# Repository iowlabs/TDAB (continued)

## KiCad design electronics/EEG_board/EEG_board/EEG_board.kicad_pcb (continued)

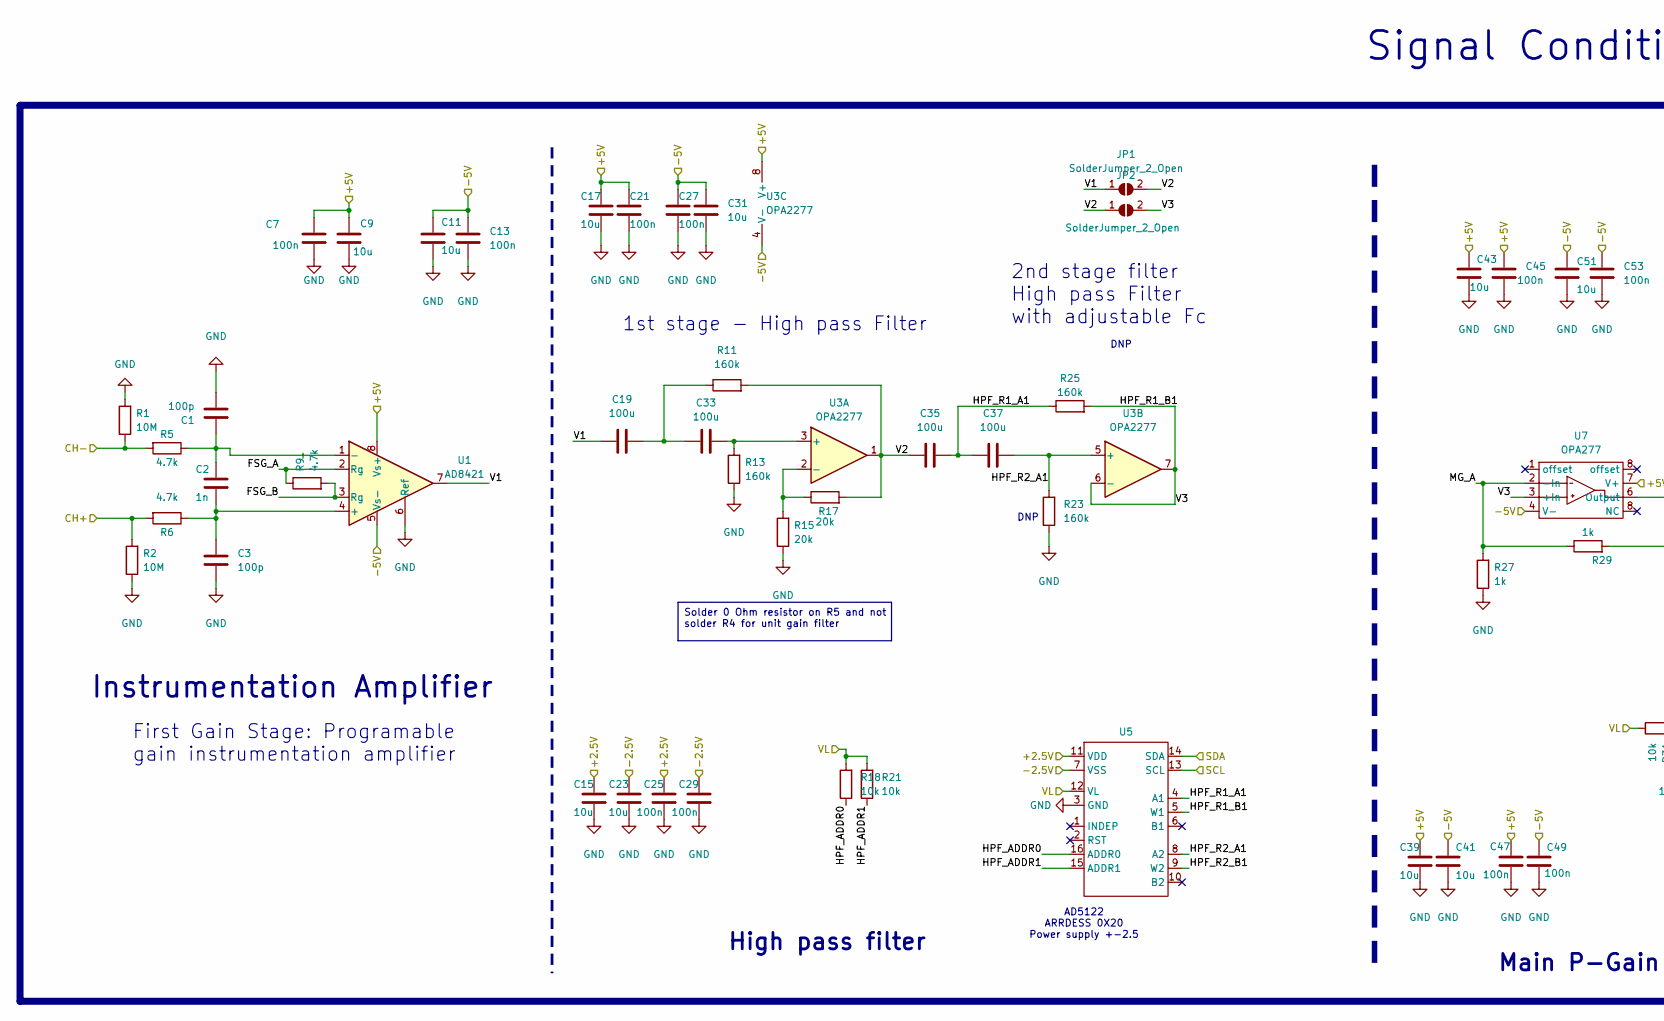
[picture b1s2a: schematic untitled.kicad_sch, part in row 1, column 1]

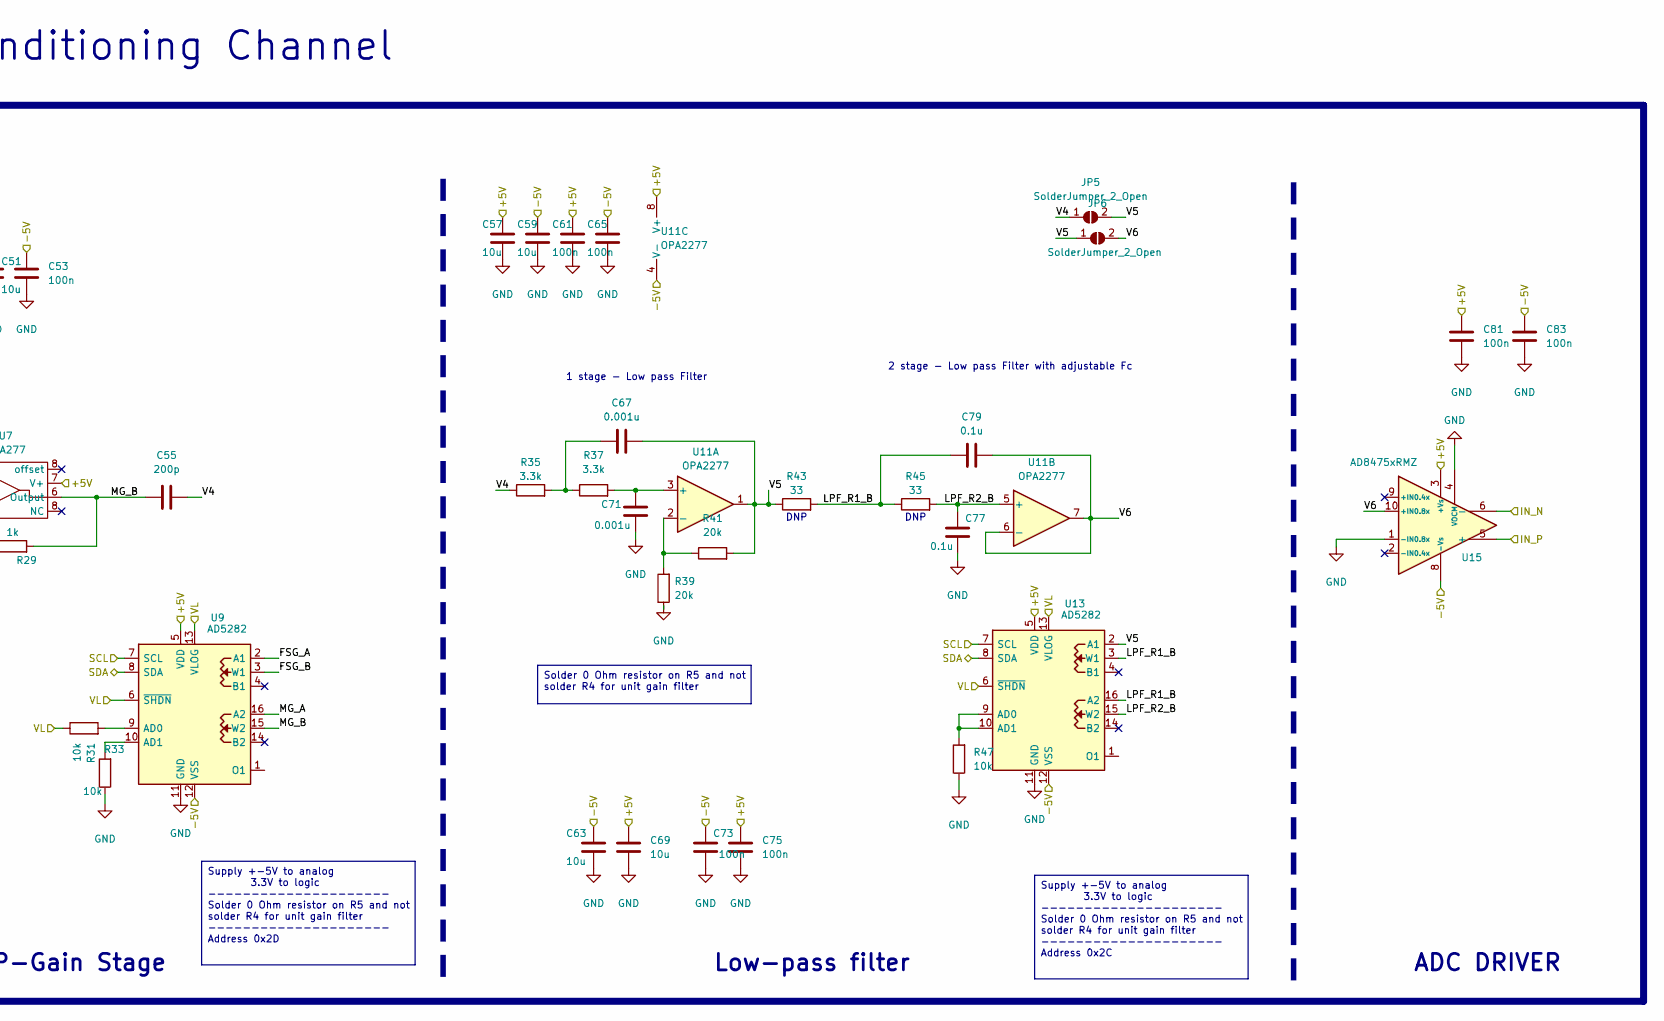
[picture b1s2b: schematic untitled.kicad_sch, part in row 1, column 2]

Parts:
C1, C3: 100p; C_0603_1608Metric
C2: 1n; C_0603_1608Metric
C7, C13, C21, C25, C27, C29, C45, C47, C49, C53, C61, C65, C73, C75, C81, C83: 100n; C_0603_1608Metric
C9, C11, C15, C17, C23, C31, C39, C41, C43, C51, C57, C59, C63, C69: 10u; C_0805_2012Metric
C19, C33, C35, C37: 100u; C_1206_3216Metric
C55: 200p; C_0603_1608Metric
C67, C71: 0.001u; C_0603_1608Metric
C77, C79: 0.1u; C_0603_1608Metric
JP1, JP2, JP5, JP6: SolderJumper_2_Open; SolderJumper-2_P1.3mm_Open_RoundedPad1.0x1.5mm
R1, R2: 10M; R_0603_1608Metric
R5, R6, R9: 4.7k; R_0603_1608Metric
R11, R13, R23, R25: 160k; R_0603_1608Metric
R15, R17, R39, R41: 20k; R_0603_1608Metric
R18, R21, R31, R33, R47: 10k; R_0603_1608Metric
R27, R29: 1k; R_0603_1608Metric
R35, R37: 3.3k; R_0603_1608Metric
R43, R45: 33; R_0603_1608Metric
U1: AD8421; SOIC-8_3.9x4.9mm_P1.27mm
U3, U11: OPA2277; SOIC-8_3.9x4.9mm_P1.27mm
U5: TSSOP-16_4.4x5mm_P0.65mm
U7: OPA277; SOIC-8_3.9x4.9mm_P1.27mm
U9, U13: AD5282; TSSOP-16_4.4x5mm_P0.65mm
U15: AD8475xRMZ; MSOP-10_3x3mm_P0.5mm

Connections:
+2.5V: C15.1, C25.1, U5.11 (VDD); also elsewhere on the board
+5V: C7.1, C9.1, C17.2, C21.1, C39.1, C43.1, C45.1, C47.1, C57.1, C61.1, C69.1, C75.1, C81.1, U1.8 (Vs+), U3.8 (V+), U7.7 (V+), U9.5 (VDD), U11.8 (V+), U13.5 (VDD), U15.3 (+Vs); also elsewhere on the board
-2.5V: C23.1, C29.1, U5.7 (VSS); also elsewhere on the board
-5V: C11.1, C13.1, C27.1, C31.1, C41.1, C49.1, C51.1, C53.1, C59.1, C63.1, C65.1, C73.1, C83.1, U1.5 (Vs-), U3.4 (V-), U7.4 (V-), U9.12 (VSS), U11.4 (V-), U13.12 (VSS), U15.8 (-Vs); also elsewhere on the board
/PPBF_CHANNEL1/FSG_A: R9.1, U1.2 (Rg), U9.2 (A1)
/PPBF_CHANNEL1/FSG_B: R9.2, U1.3 (Rg), U9.3 (W1)
/PPBF_CHANNEL1/HPF_ADDR0: R18.1, U5.16 (ADDR0)
/PPBF_CHANNEL1/HPF_ADDR1: R21.1, U5.15 (ADDR1)
/PPBF_CHANNEL1/HPF_R1_A1: C35.2, C37.1, R25.1, U5.4 (A1)
/PPBF_CHANNEL1/HPF_R1_B1: JP2.2 (B), R25.2, U3.6 (-), U3.7, U5.5 (W1), U7.3 (+In)
/PPBF_CHANNEL1/HPF_R2_A1: C37.2, R23.2, U3.5 (+), U5.8 (A2)
/PPBF_CHANNEL1/HPF_R2_B1: U5.9 (W2)
/PPBF_CHANNEL1/LPF_R1_B: C79.1, R43.2, R45.1, U13.3 (W1), U13.16 (A2)
/PPBF_CHANNEL1/LPF_R2_B: C77.1, R45.2, U11.5 (+), U13.15 (W2)
/PPBF_CHANNEL1/MG_A: R27.2, R29.1, U7.2 (-In), U9.16 (A2)
/PPBF_CHANNEL1/MG_B: C55.1, R29.2, U7.6 (Output), U9.15 (W2)
/PPBF_CHANNEL1/V1: C19.1, JP1.1 (A), U1.7
/PPBF_CHANNEL1/V2: C35.1, JP1.2 (B), JP2.1 (A), R11.2, R17.2, U3.1
/PPBF_CHANNEL1/V4: C55.2, JP5.1 (A), R35.1
/PPBF_CHANNEL1/V5: C67.2, JP5.2 (B), JP6.1 (A), R41.2, R43.1, U11.1, U13.2 (A1)
/PPBF_CHANNEL1/V6: C79.2, JP6.2 (B), U11.6 (-), U11.7, U15.10 (+IN0.8x)
CH2_+: R2.2, R6.2; also elsewhere on the board
CH2_-: R1.1, R5.2; also elsewhere on the board
GND: C1.2, C3.2, C7.2, C9.2, C11.2, C13.2, C15.2, C17.1, C21.2, C23.2, C25.2, C27.2, C29.2, C31.2, C39.2, C41.2, C43.2, C45.2, C47.2, C49.2, C51.2, C53.2, C57.2, C59.2, C61.2, C63.2, C65.2, C69.2, C71.2, C73.2, C75.2, C77.2, C81.2, C83.2, R1.2, R2.1, R13.1, R15.1, R23.1, R27.1, R33.1, R39.1, R47.1, U1.6 (Ref), U5.3 (GND), U9.11 (GND), U13.11 (GND), U15.1 (-IN0.8x), U15.4 (VOCM); also elsewhere on the board
IN2N: U15.6 (-); also elsewhere on the board
IN2P: U15.5 (+); also elsewhere on the board
unnamed: C19.2, C33.1, R11.1
unnamed: C67.1, R35.2, R37.1
unnamed: C2.2, C3.1, R6.1, U1.4 (+)
unnamed: C1.1, C2.1, R5.1, U1.1 (-)
unnamed: C33.2, R13.2, U3.3 (+)
unnamed: R15.2, R17.1, U3.2 (-)
unnamed: R31.2, U9.9 (AD0)
unnamed: R33.2, U9.10 (AD1)
unnamed: C71.1, R37.2, U11.3 (+)
unnamed: R39.2, R41.1, U11.2 (-)
unnamed: R47.2, U13.9 (AD0), U13.10 (AD1)
SCL_CH2: U5.13 (SCL), U9.7 (SCL), U13.7 (SCL); also elsewhere on the board
SDA_CH2: U5.14 (SDA), U9.8 (SDA), U13.8 (SDA); also elsewhere on the board
VL: R18.2, R21.2, R31.1, U5.12 (VL), U9.6 (~SHDN), U9.13 (VLOG), U13.6 (~SHDN), U13.13 (VLOG); also elsewhere on the board

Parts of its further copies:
C4, C6, C108, C110, C150, C152, C192, C194, C234, C236: 100p; C_0603_1608Metric
C5, C109, C151, C193, C235: 1n; C_0603_1608Metric
C8, C10, C16, C18, C22, C24, C40, C42, C46, C50, C58, C60, C70, C72, C112, C113, C115, C116, C119, C123, C127, C128, C129, C133, C136, C137, C139, C142, C154, C155, C157, C158, C161, C165, C169, C170, C171, C175, C178, C179, C181, C184, C196, C197, C199, C200, C203, C207, C211, C212, C213, C217, C220, C221, C223, C226, C238, C239, C241, C242, C245, C249, C253, C254, C255, C259, C262, C263, C265, C268: 10u; C_0805_2012Metric
C12, C14, C26, C30, C32, C34, C44, C48, C52, C54, C64, C68, C74, C76, C82, C84, C111, C114, C118, C120, C121, C122, C130, C131, C132, C134, C138, C140, C144, C145, C148, C149, C153, C156, C160, C162, C163, C164, C172, C173, C174, C176, C180, C182, C186, C187, C190, C191, C195, C198, C202, C204, C205, C206, C214, C215, C216, C218, C222, C224, C228, C229, C232, C233, C237, C240, C244, C246, C247, C248, C256, C257, C258, C260, C264, C266, C270, C271, C274, C275: 100n; C_0603_1608Metric
C20, C28, C36, C38, C117, C124, C125, C126, C159, C166, C167, C168, C201, C208, C209, C210, C243, C250, C251, C252: 100u; C_1206_3216Metric
C56, C135, C177, C219, C261: 200p; C_0603_1608Metric
C62, C66, C141, C143, C183, C185, C225, C227, C267, C269: 0.001u; C_0603_1608Metric
C78, C80, C146, C147, C188, C189, C230, C231, C272, C273: 0.1u; C_0603_1608Metric
JP3, JP4, JP7, JP8, JP9, JP10, JP11, JP12, JP13, JP14, JP15, JP16, JP17, JP18, JP19, JP20, JP21, JP22, JP23, JP24: SolderJumper_2_Open; SolderJumper-2_P1.3mm_Open_RoundedPad1.0x1.5mm
R3, R4, R74, R75, R98, R99, R122, R123, R146, R147: 10M; R_0603_1608Metric
R7, R8, R10, R76, R77, R78, R100, R101, R102, R124, R125, R126, R148, R149, R150: 4.7k; R_0603_1608Metric
R12, R16, R24, R26, R79, R80, R85, R86, R103, R104, R109, R110, R127, R128, R133, R134, R151, R152, R157, R158: 160k; R_0603_1608Metric
R14, R19, R40, R42, R81, R82, R93, R94, R105, R106, R117, R118, R129, R130, R141, R142, R153, R154, R165, R166: 20k; R_0603_1608Metric
R20, R22, R32, R34, R48, R83, R84, R89, R90, R97, R107, R108, R113, R114, R121, R131, R132, R137, R138, R145, R155, R156, R161, R162, R169: 10k; R_0603_1608Metric
R28, R30, R87, R88, R111, R112, R135, R136, R159, R160: 1k; R_0603_1608Metric
R36, R38, R91, R92, R115, R116, R139, R140, R163, R164: 3.3k; R_0603_1608Metric
R44, R46, R95, R96, R119, R120, R143, R144, R167, R168: 33; R_0603_1608Metric
U2, U24, U32, U40, U48: AD8421; SOIC-8_3.9x4.9mm_P1.27mm
U4, U12, U25, U29, U33, U37, U41, U45, U49, U53: OPA2277; SOIC-8_3.9x4.9mm_P1.27mm
U6, U26, U34, U42, U50: TSSOP-16_4.4x5mm_P0.65mm
U8, U27, U35, U43, U51: OPA277; SOIC-8_3.9x4.9mm_P1.27mm
U10, U14, U28, U30, U36, U38, U44, U46, U52, U54: AD5282; TSSOP-16_4.4x5mm_P0.65mm
U16, U31, U39, U47, U55: AD8475xRMZ; MSOP-10_3x3mm_P0.5mm

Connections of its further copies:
+2.5V: C18.1, C30.1, C115.1, C120.1, C157.1, C162.1, C199.1, C204.1, C241.1, C246.1, U6.11 (VDD), U26.11 (VDD), U34.11 (VDD), U42.11 (VDD), U50.11 (VDD); also elsewhere on the board
+5V: C8.1, C12.1, C16.2, C26.1, C40.1, C44.1, C46.1, C52.1, C58.1, C64.1, C72.1, C76.1, C82.1, C111.1, C112.1, C116.2, C118.1, C127.1, C129.1, C130.1, C131.1, C136.1, C138.1, C142.1, C145.1, C148.1, C153.1, C154.1, C158.2, C160.1, C169.1, C171.1, C172.1, C173.1, C178.1, C180.1, C184.1, C187.1, C190.1, C195.1, C196.1, C200.2, C202.1, C211.1, C213.1, C214.1, C215.1, C220.1, C222.1, C226.1, C229.1, C232.1, C237.1, C238.1, C242.2, C244.1, C253.1, C255.1, C256.1, C257.1, C262.1, C264.1, C268.1, C271.1, C274.1, U2.8 (Vs+), U4.8 (V+), U8.7 (V+), U10.5 (VDD), U12.8 (V+), U14.5 (VDD), U16.3 (+Vs), U24.8 (Vs+), U25.8 (V+), U27.7 (V+), U28.5 (VDD), U29.8 (V+), U30.5 (VDD), U31.3 (+Vs), U32.8 (Vs+), U33.8 (V+), U35.7 (V+), U36.5 (VDD), U37.8 (V+), U38.5 (VDD), U39.3 (+Vs), U40.8 (Vs+), U41.8 (V+), U43.7 (V+), U44.5 (VDD), U45.8 (V+), U46.5 (VDD), U47.3 (+Vs), U48.8 (Vs+), U49.8 (V+), U51.7 (V+), U52.5 (VDD), U53.8 (V+), U54.5 (VDD), U55.3 (+Vs); also elsewhere on the board
-2.5V: C24.1, C34.1, C119.1, C122.1, C161.1, C164.1, C203.1, C206.1, C245.1, C248.1, U6.7 (VSS), U26.7 (VSS), U34.7 (VSS), U42.7 (VSS), U50.7 (VSS); also elsewhere on the board
-5V: C10.1, C14.1, C22.1, C32.1, C42.1, C48.1, C50.1, C54.1, C60.1, C68.1, C70.1, C74.1, C84.1, C113.1, C114.1, C121.1, C123.1, C128.1, C132.1, C133.1, C134.1, C137.1, C139.1, C140.1, C144.1, C149.1, C155.1, C156.1, C163.1, C165.1, C170.1, C174.1, C175.1, C176.1, C179.1, C181.1, C182.1, C186.1, C191.1, C197.1, C198.1, C205.1, C207.1, C212.1, C216.1, C217.1, C218.1, C221.1, C223.1, C224.1, C228.1, C233.1, C239.1, C240.1, C247.1, C249.1, C254.1, C258.1, C259.1, C260.1, C263.1, C265.1, C266.1, C270.1, C275.1, U2.5 (Vs-), U4.4 (V-), U8.4 (V-), U10.12 (VSS), U12.4 (V-), U14.12 (VSS), U16.8 (-Vs), U24.5 (Vs-), U25.4 (V-), U27.4 (V-), U28.12 (VSS), U29.4 (V-), U30.12 (VSS), U31.8 (-Vs), U32.5 (Vs-), U33.4 (V-), U35.4 (V-), U36.12 (VSS), U37.4 (V-), U38.12 (VSS), U39.8 (-Vs), U40.5 (Vs-), U41.4 (V-), U43.4 (V-), U44.12 (VSS), U45.4 (V-), U46.12 (VSS), U47.8 (-Vs), U48.5 (Vs-), U49.4 (V-), U51.4 (V-), U52.12 (VSS), U53.4 (V-), U54.12 (VSS), U55.8 (-Vs); also elsewhere on the board
/PPBF_CHANNEL2/FSG_A: R78.1, U24.2 (Rg), U28.2 (A1)
/PPBF_CHANNEL2/FSG_B: R78.2, U24.3 (Rg), U28.3 (W1)
/PPBF_CHANNEL2/HPF_ADDR0: R83.1, U26.16 (ADDR0)
/PPBF_CHANNEL2/HPF_ADDR1: R84.1, U26.15 (ADDR1)
/PPBF_CHANNEL2/HPF_R1_A1: C125.2, C126.1, R86.1, U26.4 (A1)
/PPBF_CHANNEL2/HPF_R1_B1: JP10.2 (B), R86.2, U25.6 (-), U25.7, U26.5 (W1), U27.3 (+In)
/PPBF_CHANNEL2/HPF_R2_A1: C126.2, R85.2, U25.5 (+), U26.8 (A2)
/PPBF_CHANNEL2/HPF_R2_B1: U26.9 (W2)
/PPBF_CHANNEL2/LPF_R1_B: C147.1, R95.2, R96.1, U30.3 (W1), U30.16 (A2)
/PPBF_CHANNEL2/LPF_R2_B: C146.1, R96.2, U29.5 (+), U30.15 (W2)
/PPBF_CHANNEL2/MG_A: R87.2, R88.1, U27.2 (-In), U28.16 (A2)
/PPBF_CHANNEL2/MG_B: C135.1, R88.2, U27.6 (Output), U28.15 (W2)
/PPBF_CHANNEL2/V1: C117.1, JP9.1 (A), U24.7
/PPBF_CHANNEL2/V2: C125.1, JP9.2 (B), JP10.1 (A), R79.2, R82.2, U25.1
/PPBF_CHANNEL2/V4: C135.2, JP11.1 (A), R91.1
/PPBF_CHANNEL2/V5: C141.2, JP11.2 (B), JP12.1 (A), R94.2, R95.1, U29.1, U30.2 (A1)
/PPBF_CHANNEL2/V6: C147.2, JP12.2 (B), U29.6 (-), U29.7, U31.10 (+IN0.8x)
/PPBF_CHANNEL3/FSG_A: R102.1, U32.2 (Rg), U36.2 (A1)
/PPBF_CHANNEL3/FSG_B: R102.2, U32.3 (Rg), U36.3 (W1)
/PPBF_CHANNEL3/HPF_ADDR0: R107.1, U34.16 (ADDR0)
/PPBF_CHANNEL3/HPF_ADDR1: R108.1, U34.15 (ADDR1)
/PPBF_CHANNEL3/HPF_R1_A1: C167.2, C168.1, R110.1, U34.4 (A1)
/PPBF_CHANNEL3/HPF_R1_B1: JP14.2 (B), R110.2, U33.6 (-), U33.7, U34.5 (W1), U35.3 (+In)
/PPBF_CHANNEL3/HPF_R2_A1: C168.2, R109.2, U33.5 (+), U34.8 (A2)
/PPBF_CHANNEL3/HPF_R2_B1: U34.9 (W2)
/PPBF_CHANNEL3/LPF_R1_B: C189.1, R119.2, R120.1, U38.3 (W1), U38.16 (A2)
/PPBF_CHANNEL3/LPF_R2_B: C188.1, R120.2, U37.5 (+), U38.15 (W2)
/PPBF_CHANNEL3/MG_A: R111.2, R112.1, U35.2 (-In), U36.16 (A2)
/PPBF_CHANNEL3/MG_B: C177.1, R112.2, U35.6 (Output), U36.15 (W2)
/PPBF_CHANNEL3/V1: C159.1, JP13.1 (A), U32.7
/PPBF_CHANNEL3/V2: C167.1, JP13.2 (B), JP14.1 (A), R103.2, R106.2, U33.1
/PPBF_CHANNEL3/V4: C177.2, JP15.1 (A), R115.1
/PPBF_CHANNEL3/V5: C183.2, JP15.2 (B), JP16.1 (A), R118.2, R119.1, U37.1, U38.2 (A1)
/PPBF_CHANNEL3/V6: C189.2, JP16.2 (B), U37.6 (-), U37.7, U39.10 (+IN0.8x)
/PPBF_CHANNEL4/FSG_A: R126.1, U40.2 (Rg), U44.2 (A1)
/PPBF_CHANNEL4/FSG_B: R126.2, U40.3 (Rg), U44.3 (W1)
/PPBF_CHANNEL4/HPF_ADDR0: R131.1, U42.16 (ADDR0)
/PPBF_CHANNEL4/HPF_ADDR1: R132.1, U42.15 (ADDR1)
/PPBF_CHANNEL4/HPF_R1_A1: C209.2, C210.1, R134.1, U42.4 (A1)
/PPBF_CHANNEL4/HPF_R1_B1: JP18.2 (B), R134.2, U41.6 (-), U41.7, U42.5 (W1), U43.3 (+In)
/PPBF_CHANNEL4/HPF_R2_A1: C210.2, R133.2, U41.5 (+), U42.8 (A2)
/PPBF_CHANNEL4/HPF_R2_B1: U42.9 (W2)
/PPBF_CHANNEL4/LPF_R1_B: C231.1, R143.2, R144.1, U46.3 (W1), U46.16 (A2)
/PPBF_CHANNEL4/LPF_R2_B: C230.1, R144.2, U45.5 (+), U46.15 (W2)
/PPBF_CHANNEL4/MG_A: R135.2, R136.1, U43.2 (-In), U44.16 (A2)
/PPBF_CHANNEL4/MG_B: C219.1, R136.2, U43.6 (Output), U44.15 (W2)
/PPBF_CHANNEL4/V1: C201.1, JP17.1 (A), U40.7
/PPBF_CHANNEL4/V2: C209.1, JP17.2 (B), JP18.1 (A), R127.2, R130.2, U41.1
/PPBF_CHANNEL4/V4: C219.2, JP19.1 (A), R139.1
/PPBF_CHANNEL4/V5: C225.2, JP19.2 (B), JP20.1 (A), R142.2, R143.1, U45.1, U46.2 (A1)
/PPBF_CHANNEL4/V6: C231.2, JP20.2 (B), U45.6 (-), U45.7, U47.10 (+IN0.8x)
/PPBF_CHANNEL5/FSG_A: R150.1, U48.2 (Rg), U52.2 (A1)
/PPBF_CHANNEL5/FSG_B: R150.2, U48.3 (Rg), U52.3 (W1)
/PPBF_CHANNEL5/HPF_ADDR0: R155.1, U50.16 (ADDR0)
/PPBF_CHANNEL5/HPF_ADDR1: R156.1, U50.15 (ADDR1)
/PPBF_CHANNEL5/HPF_R1_A1: C251.2, C252.1, R158.1, U50.4 (A1)
/PPBF_CHANNEL5/HPF_R1_B1: JP22.2 (B), R158.2, U49.6 (-), U49.7, U50.5 (W1), U51.3 (+In)
/PPBF_CHANNEL5/HPF_R2_A1: C252.2, R157.2, U49.5 (+), U50.8 (A2)
/PPBF_CHANNEL5/HPF_R2_B1: U50.9 (W2)
/PPBF_CHANNEL5/LPF_R1_B: C273.1, R167.2, R168.1, U54.3 (W1), U54.16 (A2)
/PPBF_CHANNEL5/LPF_R2_B: C272.1, R168.2, U53.5 (+), U54.15 (W2)
/PPBF_CHANNEL5/MG_A: R159.2, R160.1, U51.2 (-In), U52.16 (A2)
/PPBF_CHANNEL5/MG_B: C261.1, R160.2, U51.6 (Output), U52.15 (W2)
/PPBF_CHANNEL5/V1: C243.1, JP21.1 (A), U48.7
/PPBF_CHANNEL5/V2: C251.1, JP21.2 (B), JP22.1 (A), R151.2, R154.2, U49.1
/PPBF_CHANNEL5/V4: C261.2, JP23.1 (A), R163.1
/PPBF_CHANNEL5/V5: C267.2, JP23.2 (B), JP24.1 (A), R166.2, R167.1, U53.1, U54.2 (A1)
/PPBF_CHANNEL5/V6: C273.2, JP24.2 (B), U53.6 (-), U53.7, U55.10 (+IN0.8x)
/PPBF_CHANNEL/FSG_A: R10.1, U2.2 (Rg), U10.2 (A1)
/PPBF_CHANNEL/FSG_B: R10.2, U2.3 (Rg), U10.3 (W1)
/PPBF_CHANNEL/HPF_ADDR0: R20.1, U6.16 (ADDR0)
/PPBF_CHANNEL/HPF_ADDR1: R22.1, U6.15 (ADDR1)
/PPBF_CHANNEL/HPF_R1_A1: C36.2, C38.1, R26.1, U6.4 (A1)
/PPBF_CHANNEL/HPF_R1_B1: JP4.2 (B), R26.2, U4.6 (-), U4.7, U6.5 (W1), U8.3 (+In)
/PPBF_CHANNEL/HPF_R2_A1: C38.2, R24.2, U4.5 (+), U6.8 (A2)
/PPBF_CHANNEL/HPF_R2_B1: U6.9 (W2)
/PPBF_CHANNEL/LPF_R1_B: C80.1, R44.2, R46.1, U14.3 (W1), U14.16 (A2)
/PPBF_CHANNEL/LPF_R2_B: C78.1, R46.2, U12.5 (+), U14.15 (W2)
/PPBF_CHANNEL/MG_A: R28.2, R30.1, U8.2 (-In), U10.16 (A2)
/PPBF_CHANNEL/MG_B: C56.1, R30.2, U8.6 (Output), U10.15 (W2)
/PPBF_CHANNEL/V1: C20.1, JP3.1 (A), U2.7
/PPBF_CHANNEL/V2: C36.1, JP3.2 (B), JP4.1 (A), R16.2, R19.2, U4.1
/PPBF_CHANNEL/V4: C56.2, JP7.1 (A), R36.1
/PPBF_CHANNEL/V5: C66.2, JP7.2 (B), JP8.1 (A), R42.2, R44.1, U12.1, U14.2 (A1)
/PPBF_CHANNEL/V6: C80.2, JP8.2 (B), U12.6 (-), U12.7, U16.10 (+IN0.8x)
CH1_+: R4.2, R8.2; also elsewhere on the board
CH1_-: R3.1, R7.2; also elsewhere on the board
CH3_+: R75.2, R77.2; also elsewhere on the board
CH3_-: R74.1, R76.2; also elsewhere on the board
CH4_+: R99.2, R101.2; also elsewhere on the board
CH4_-: R98.1, R100.2; also elsewhere on the board
CH5_+: R123.2, R125.2; also elsewhere on the board
CH5_-: R122.1, R124.2; also elsewhere on the board
CH6_+: R147.2, R149.2; also elsewhere on the board
CH6_-: R146.1, R148.2; also elsewhere on the board
GND: C4.2, C6.2, C8.2, C10.2, C12.2, C14.2, C16.1, C18.2, C22.2, C24.2, C26.2, C30.2, C32.2, C34.2, C40.2, C42.2, C44.2, C46.2, C48.2, C50.2, C52.2, C54.2, C58.2, C60.2, C62.2, C64.2, C68.2, C70.2, C72.2, C74.2, C76.2, C78.2, C82.2, C84.2, C108.2, C110.2, C111.2, C112.2, C113.2, C114.2, C115.2, C116.1, C118.2, C119.2, C120.2, C121.2, C122.2, C123.2, C127.2, C128.2, C129.2, C130.2, C131.2, C132.2, C133.2, C134.2, C136.2, C137.2, C138.2, C139.2, C140.2, C142.2, C143.2, C144.2, C145.2, C146.2, C148.2, C149.2, C150.2, C152.2, C153.2, C154.2, C155.2, C156.2, C157.2, C158.1, C160.2, C161.2, C162.2, C163.2, C164.2, C165.2, C169.2, C170.2, C171.2, C172.2, C173.2, C174.2, C175.2, C176.2, C178.2, C179.2, C180.2, C181.2, C182.2, C184.2, C185.2, C186.2, C187.2, C188.2, C190.2, C191.2, C192.2, C194.2, C195.2, C196.2, C197.2, C198.2, C199.2, C200.1, C202.2, C203.2, C204.2, C205.2, C206.2, C207.2, C211.2, C212.2, C213.2, C214.2, C215.2, C216.2, C217.2, C218.2, C220.2, C221.2, C222.2, C223.2, C224.2, C226.2, C227.2, C228.2, C229.2, C230.2, C232.2, C233.2, C234.2, C236.2, C237.2, C238.2, C239.2, C240.2, C241.2, C242.1, C244.2, C245.2, C246.2, C247.2, C248.2, C249.2, C253.2, C254.2, C255.2, C256.2, C257.2, C258.2, C259.2, C260.2, C262.2, C263.2, C264.2, C265.2, C266.2, C268.2, C269.2, C270.2, C271.2, C272.2, C274.2, C275.2, R3.2, R4.1, R12.1, R14.1, R24.1, R28.1, R34.1, R40.1, R48.1, R74.2, R75.1, R80.1, R81.1, R85.1, R87.1, R90.1, R93.1, R97.1, R98.2, R99.1, R104.1, R105.1, R109.1, R111.1, R114.1, R117.1, R121.1, R122.2, R123.1, R128.1, R129.1, R133.1, R135.1, R138.1, R141.1, R145.1, R146.2, R147.1, R152.1, R153.1, R157.1, R159.1, R162.1, R165.1, R169.1, U2.6 (Ref), U6.3 (GND), U10.11 (GND), U14.11 (GND), U16.1 (-IN0.8x), U16.4 (VOCM), U24.6 (Ref), U26.3 (GND), U28.11 (GND), U30.11 (GND), U31.1 (-IN0.8x), U31.4 (VOCM), U32.6 (Ref), U34.3 (GND), U36.11 (GND), U38.11 (GND), U39.1 (-IN0.8x), U39.4 (VOCM), U40.6 (Ref), U42.3 (GND), U44.11 (GND), U46.11 (GND), U47.1 (-IN0.8x), U47.4 (VOCM), U48.6 (Ref), U50.3 (GND), U52.11 (GND), U54.11 (GND), U55.1 (-IN0.8x), U55.4 (VOCM); also elsewhere on the board
IN1N: U16.6 (-); also elsewhere on the board
IN1P: U16.5 (+); also elsewhere on the board
IN3N: U31.6 (-); also elsewhere on the board
IN3P: U31.5 (+); also elsewhere on the board
IN4N: U39.6 (-); also elsewhere on the board
IN4P: U39.5 (+); also elsewhere on the board
IN5N: U47.6 (-); also elsewhere on the board
IN5P: U47.5 (+); also elsewhere on the board
IN6N: U55.6 (-); also elsewhere on the board
IN6P: U55.5 (+); also elsewhere on the board
unnamed: C20.2, C28.1, R16.1
unnamed: C66.1, R36.2, R38.1
unnamed: C117.2, C124.1, R79.1
unnamed: C141.1, R91.2, R92.1
unnamed: C159.2, C166.1, R103.1
unnamed: C183.1, R115.2, R116.1
unnamed: C201.2, C208.1, R127.1
unnamed: C225.1, R139.2, R140.1
unnamed: C243.2, C250.1, R151.1
unnamed: C267.1, R163.2, R164.1
unnamed: C5.2, C6.1, R8.1, U2.4 (+)
unnamed: C4.1, C5.1, R7.1, U2.1 (-)
unnamed: C28.2, R12.2, U4.3 (+)
unnamed: R14.2, R19.1, U4.2 (-)
unnamed: R32.2, U10.9 (AD0)
unnamed: R34.2, U10.10 (AD1)
unnamed: C62.1, R38.2, U12.3 (+)
unnamed: R40.2, R42.1, U12.2 (-)
unnamed: R48.2, U14.9 (AD0), U14.10 (AD1)
unnamed: C109.2, C110.1, R77.1, U24.4 (+)
unnamed: C108.1, C109.1, R76.1, U24.1 (-)
unnamed: C124.2, R80.2, U25.3 (+)
unnamed: R81.2, R82.1, U25.2 (-)
unnamed: R89.2, U28.9 (AD0)
unnamed: R90.2, U28.10 (AD1)
unnamed: C143.1, R92.2, U29.3 (+)
unnamed: R93.2, R94.1, U29.2 (-)
unnamed: R97.2, U30.9 (AD0), U30.10 (AD1)
unnamed: C151.2, C152.1, R101.1, U32.4 (+)
unnamed: C150.1, C151.1, R100.1, U32.1 (-)
unnamed: C166.2, R104.2, U33.3 (+)
unnamed: R105.2, R106.1, U33.2 (-)
unnamed: R113.2, U36.9 (AD0)
unnamed: R114.2, U36.10 (AD1)
unnamed: C185.1, R116.2, U37.3 (+)
unnamed: R117.2, R118.1, U37.2 (-)
unnamed: R121.2, U38.9 (AD0), U38.10 (AD1)
unnamed: C193.2, C194.1, R125.1, U40.4 (+)
unnamed: C192.1, C193.1, R124.1, U40.1 (-)
unnamed: C208.2, R128.2, U41.3 (+)
unnamed: R129.2, R130.1, U41.2 (-)
unnamed: R137.2, U44.9 (AD0)
unnamed: R138.2, U44.10 (AD1)
unnamed: C227.1, R140.2, U45.3 (+)
unnamed: R141.2, R142.1, U45.2 (-)
unnamed: R145.2, U46.9 (AD0), U46.10 (AD1)
unnamed: C235.2, C236.1, R149.1, U48.4 (+)
unnamed: C234.1, C235.1, R148.1, U48.1 (-)
unnamed: C250.2, R152.2, U49.3 (+)
unnamed: R153.2, R154.1, U49.2 (-)
unnamed: R161.2, U52.9 (AD0)
unnamed: R162.2, U52.10 (AD1)
unnamed: C269.1, R164.2, U53.3 (+)
unnamed: R165.2, R166.1, U53.2 (-)
unnamed: R169.2, U54.9 (AD0), U54.10 (AD1)
SCL_CH1: U6.13 (SCL), U10.7 (SCL), U14.7 (SCL); also elsewhere on the board
SCL_CH3: U26.13 (SCL), U28.7 (SCL), U30.7 (SCL); also elsewhere on the board
SCL_CH4: U34.13 (SCL), U36.7 (SCL), U38.7 (SCL); also elsewhere on the board
SCL_CH5: U42.13 (SCL), U44.7 (SCL), U46.7 (SCL); also elsewhere on the board
SCL_CH6: U50.13 (SCL), U52.7 (SCL), U54.7 (SCL); also elsewhere on the board
SDA_CH1: U6.14 (SDA), U10.8 (SDA), U14.8 (SDA); also elsewhere on the board
SDA_CH3: U26.14 (SDA), U28.8 (SDA), U30.8 (SDA); also elsewhere on the board
SDA_CH4: U34.14 (SDA), U36.8 (SDA), U38.8 (SDA); also elsewhere on the board
SDA_CH5: U42.14 (SDA), U44.8 (SDA), U46.8 (SDA); also elsewhere on the board
SDA_CH6: U50.14 (SDA), U52.8 (SDA), U54.8 (SDA); also elsewhere on the board
VL: R20.2, R22.2, R32.1, R83.2, R84.2, R89.1, R107.2, R108.2, R113.1, R131.2, R132.2, R137.1, R155.2, R156.2, R161.1, U6.12 (VL), U10.6 (~SHDN), U10.13 (VLOG), U14.6 (~SHDN), U14.13 (VLOG), U26.12 (VL), U28.6 (~SHDN), U28.13 (VLOG), U30.6 (~SHDN), U30.13 (VLOG), U34.12 (VL), U36.6 (~SHDN), U36.13 (VLOG), U38.6 (~SHDN), U38.13 (VLOG), U42.12 (VL), U44.6 (~SHDN), U44.13 (VLOG), U46.6 (~SHDN), U46.13 (VLOG), U50.12 (VL), U52.6 (~SHDN), U52.13 (VLOG), U54.6 (~SHDN), U54.13 (VLOG); also elsewhere on the board

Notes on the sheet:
Solder 0 Ohm resistor on R5 and not solder R4 for unit gain filter
Supply +-5V to analog 3.3V to logic --------------------- Solder 0 Ohm resistor on R5 and not solder R4 for unit gain filter --------------------- Address 0x2D
Supply +-5V to analog 3.3V to logic --------------------- Solder 0 Ohm resistor on R5 and not solder R4 for unit gain filter --------------------- Address 0x2C
2nd stage filter High pass Filter with adjustable Fc
Instrumentation Amplifier
DNP
ADC DRIVER
AD5122 ARRDESS 0X20 Power supply +-2.5
Low-pass filter
2 stage - Low pass Filter with adjustable Fc
1 stage - Low pass Filter
First Gain Stage: Programable gain instrumentation amplifier
Signal Conditioning Channel
1st stage - High pass Filter
Main P-Gain Stage
High pass filter

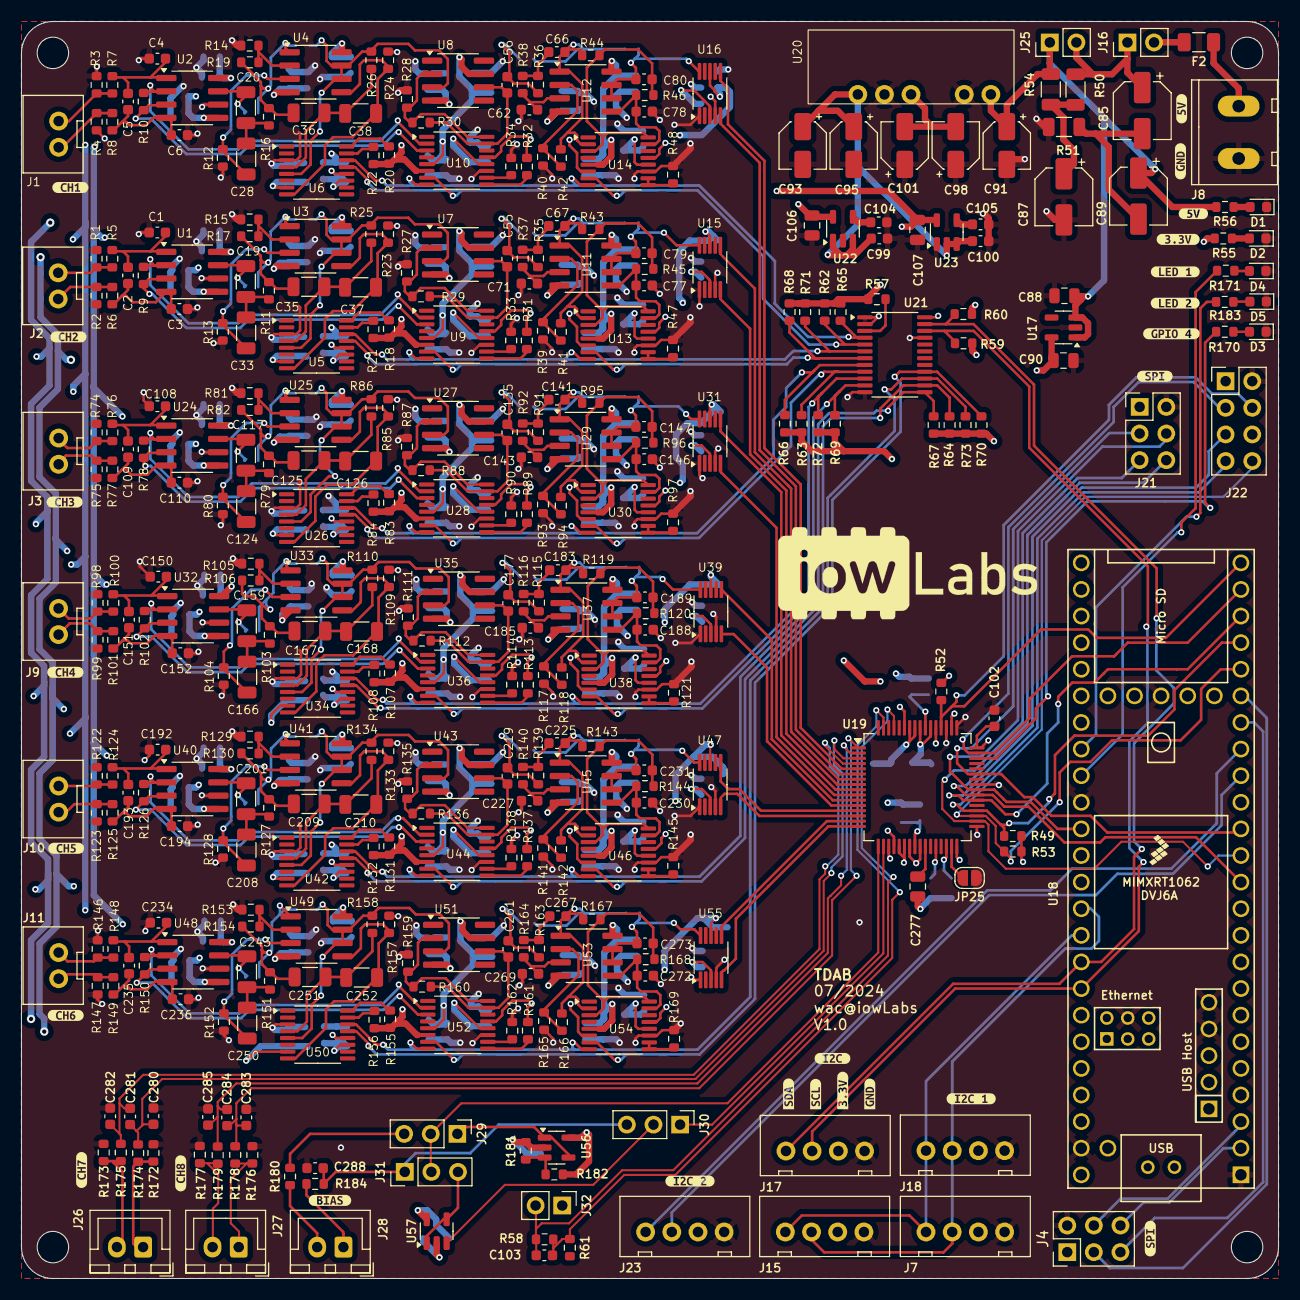
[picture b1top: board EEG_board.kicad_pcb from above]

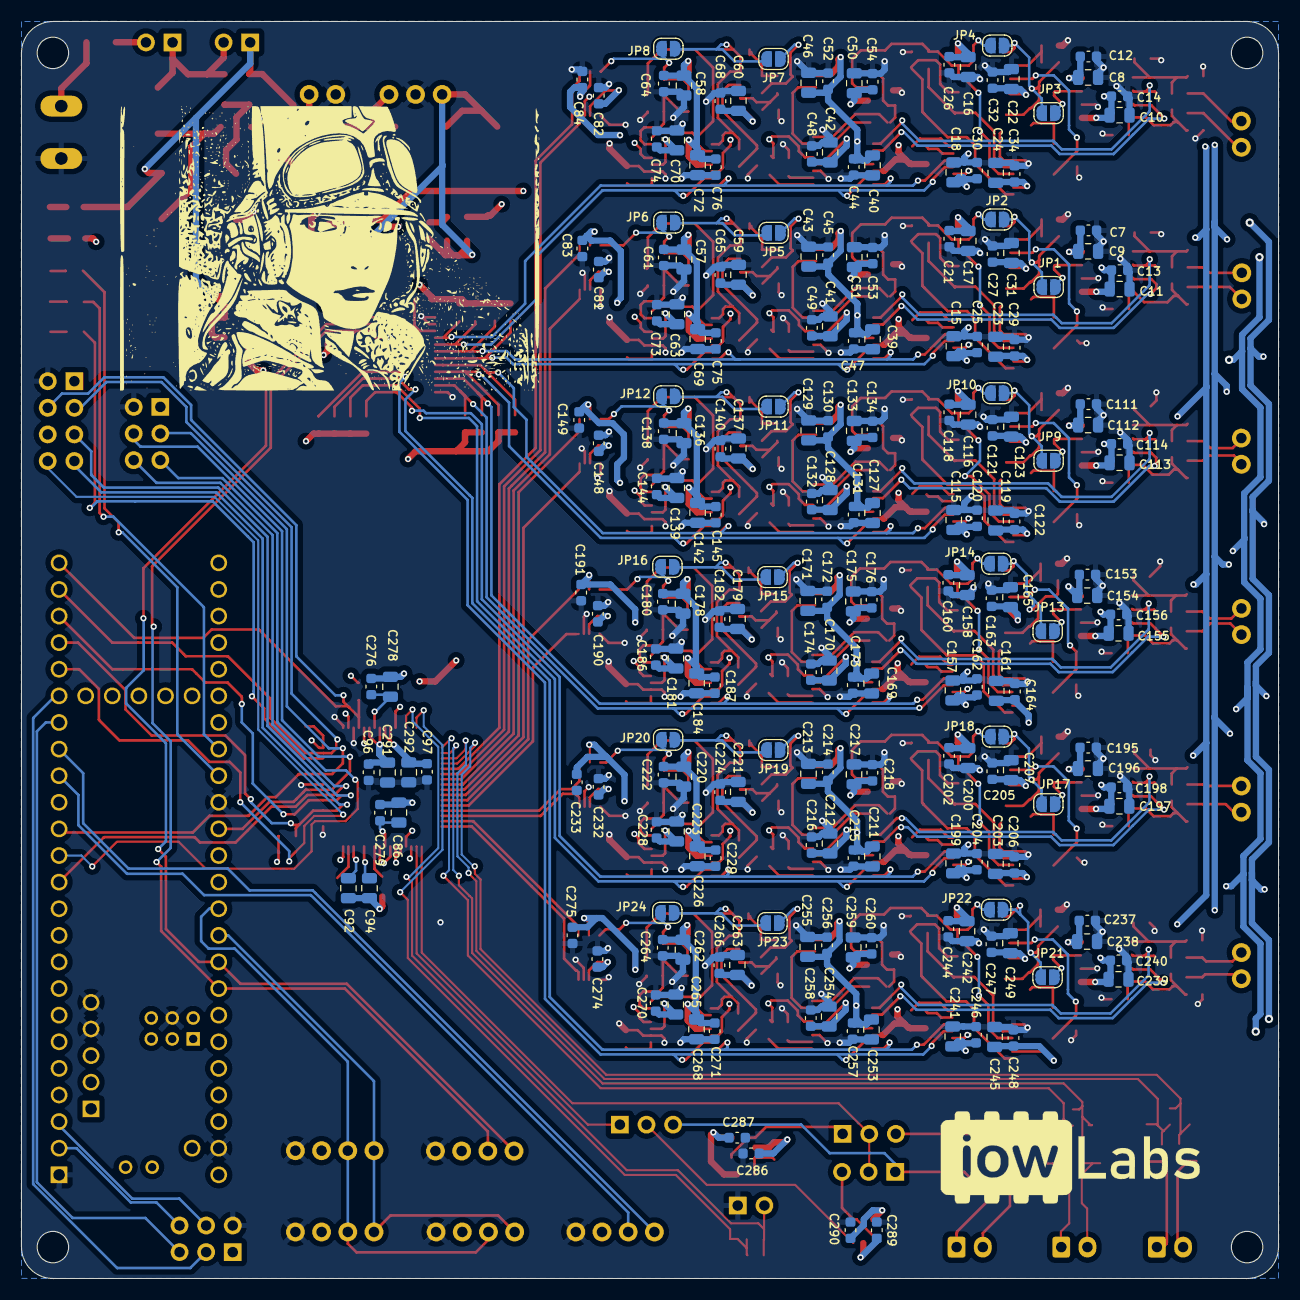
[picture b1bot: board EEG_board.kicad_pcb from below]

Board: 4 copper layers, 120.0 x 120.0 mm, 613 parts (218 on the bottom side), 266 nets.

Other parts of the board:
kibuzzard-66F1BD5D: G***; kibuzzard-66F1BD5D
kibuzzard-66F1BD73: G***; kibuzzard-66F1BD73
kibuzzard-66F1BE9F: G***; kibuzzard-66F1BE9F
kibuzzard-66F1BE81: G***; kibuzzard-66F1BE81
kibuzzard-66F1BE92: G***; kibuzzard-66F1BE92
kibuzzard-66F1BEAE: G***; kibuzzard-66F1BEAE
kibuzzard-66F1BEC6: G***; kibuzzard-66F1BEC6
kibuzzard-66F1BED1: G***; kibuzzard-66F1BED1
kibuzzard-66F1C1A7: G***; kibuzzard-66F1C1A7
kibuzzard-66F1C1B9: G***; kibuzzard-66F1C1B9
kibuzzard-66F1C1C3: G***; kibuzzard-66F1C1C3
kibuzzard-66F1C1DB: G***; kibuzzard-66F1C1DB
kibuzzard-66F1C1F0: G***; kibuzzard-66F1C1F0
kibuzzard-66F1C19C: G***; kibuzzard-66F1C19C
kibuzzard-66F1C22B: G***; kibuzzard-66F1C22B
kibuzzard-66F1C23E: G***; kibuzzard-66F1C23E
kibuzzard-66F1C29C: G***; kibuzzard-66F1C29C
kibuzzard-66F1C172: G***; kibuzzard-66F1C172
kibuzzard-66F1C187: G***; kibuzzard-66F1C187
kibuzzard-66F1C231: G***; kibuzzard-66F1C231
kibuzzard-66F1C248: G***; kibuzzard-66F1C248
kibuzzard-66F1C256: G***; kibuzzard-66F1C256
kibuzzard-66F1C265: G***; kibuzzard-66F1C265
kibuzzard-66F1C285: G***; kibuzzard-66F1C285
kibuzzard-66F4DE44: G***; kibuzzard-66F4DE44

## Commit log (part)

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2024-08-29 checking PWR traces on layout
2024-08-29 starting readme
2024-09-26 working on gui adding accel review
2024-09-26 removing .step
2025-04-29 implementing down sampling
2025-06-05 adding test adc
2025-08-19 testing core of i2c transmition
2025-09-24 versión 1 del código, considera testear comunicación y graficar en tiempo real. considera firmware y software
2025-09-24 minor changes
2025-09-24 responsive app
2025-09-25 integrating back and front end
2025-10-15 pararlel grapth
